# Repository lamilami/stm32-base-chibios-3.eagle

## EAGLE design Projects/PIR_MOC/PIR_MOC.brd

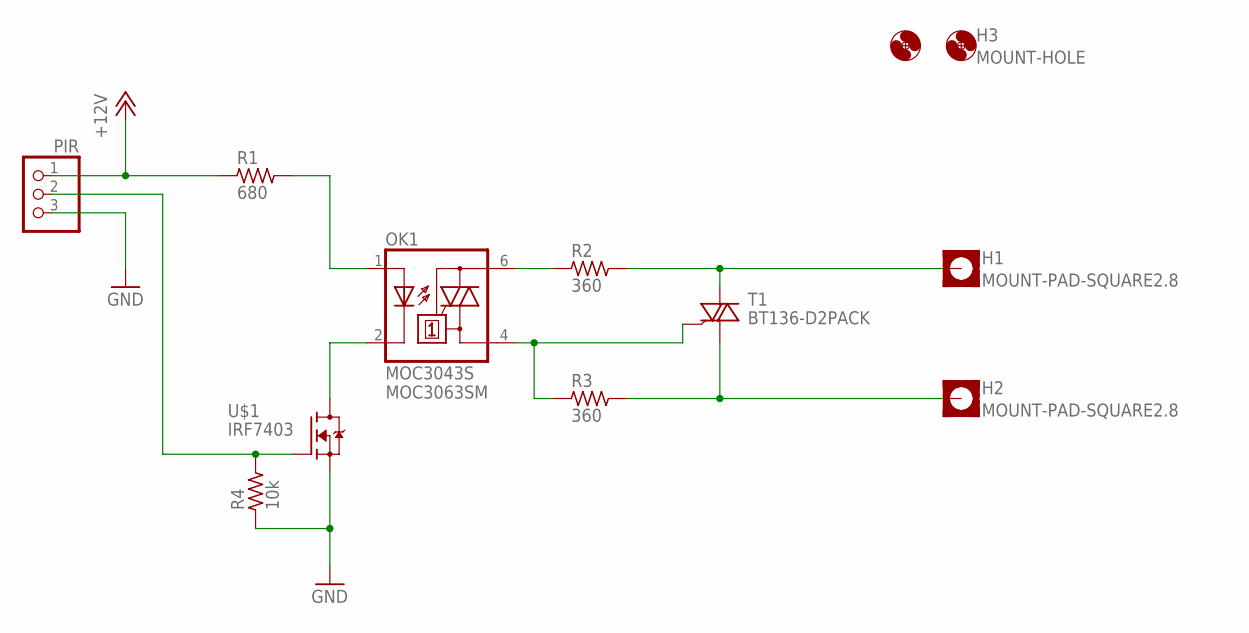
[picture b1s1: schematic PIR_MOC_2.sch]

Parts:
H1, H2: MOUNT-PAD-SQUARE2.8; 2,8-PAD-SQUARE
H3: MOUNT-HOLE; CASE_20-31_VHOLES
OK1: MOC3043S; DIL6-SMD; MPN MOC3063SM
PIR: PINHD-1X03_2.54-S; 1X03-S
R1: 680; R1206
R2, R3: 360; R1206
R4: 10k; R1206
T1: BT136-D2PACK; TO263
U$1: IRF7403; SO-8

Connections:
220_AC: H1.B2,8, R2.2, T1.3 (A2)
220_MOC_AC: OK1.6 (A2), R2.1
220_MOC_N: OK1.4 (A1), R3.1, T1.2 (G)
220_N: H2.B2,8, R3.2, T1.1 (A1)
+12V: PIR.1, R1.1
GND: PIR.3, R4.1, U$1.1 (S), U$1.2 (S), U$1.3 (S)
unnamed: OK1.2 (C), U$1.5 (D), U$1.6 (D), U$1.7 (D), U$1.8 (D)
unnamed: OK1.1 (A), R1.2
unnamed: PIR.2, R4.2, U$1.4 (G)

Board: 2 copper layers, 11 parts (0 on the bottom side), 9 nets, no tracks yet.

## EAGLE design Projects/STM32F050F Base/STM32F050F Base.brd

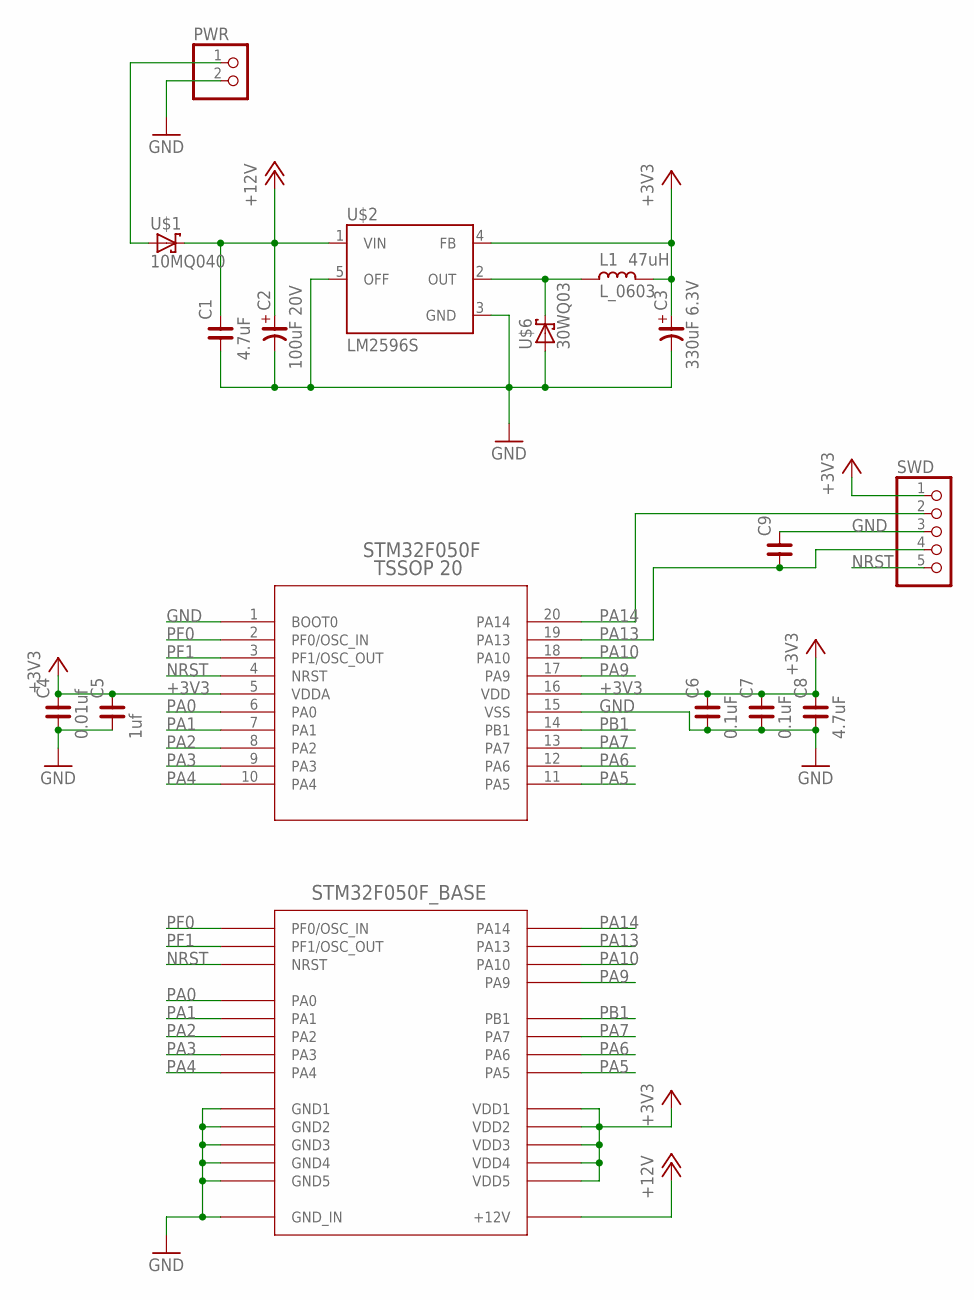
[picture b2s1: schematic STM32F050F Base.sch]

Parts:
C1, C8: 4.7uF; C1206
C2: 100uF 20V; C7343/T
C3: 330uF 6.3V; C7343/T
C4: 0.01uf; C0805
C5: 1uf; C0805
C6, C7: 0.1uF; C0805
C9: C_1206; C1206
L1: L_0603; L0603
PWR: PINHD-1X02_2.54-90°-S; 1X02/90-S
SWD: PINHD-1X05_2.54-90°-S; 1X05/90-S
U$1: 10MQ040; SMA
U$2: LM2596S; TO263-5
U$4: STM32F050F4P6; TSSOP20
U$5: STM32F050F_BASE_BASE; STM32_BASE
U$6: 30WQ03; TO252

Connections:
+3V3: C3.+, C4.2, C5.2, C6.2, C7.2, C8.2, L1.1, SWD.1, U$2.4 (FB), U$4.5 (VDDA), U$4.16 (VDD), U$5.VDD1, U$5.VDD2, U$5.VDD3, U$5.VDD4, U$5.VDD5
+12V: C1.2, C2.+, U$1.C, U$2.1 (VIN), U$5.+12V
GND: C1.1, C2.-, C3.-, C4.1, C5.1, C6.1, C7.1, C8.1, C9.2, PWR.2, SWD.3, U$2.3 (GND), U$2.5 (OFF), U$4.1 (BOOT0), U$4.15 (VSS), U$5.GND1, U$5.GND2, U$5.GND3, U$5.GND4, U$5.GND5, U$5.GND_IN, U$6.1 (A), U$6.2 (A)
unnamed: PWR.1, U$1.A
unnamed: L1.2, U$2.2 (OUT), U$6.3 (C)
NRST: SWD.5, U$4.4 (NRST), U$5.NRST
PA0: U$4.6 (PA0), U$5.PA0
PA1: U$4.7 (PA1), U$5.PA1
PA2: U$4.8 (PA2), U$5.PA2
PA3: U$4.9 (PA3), U$5.PA3
PA4: U$4.10 (PA4), U$5.PA4
PA5: U$4.11 (PA5), U$5.PA5
PA6: U$4.12 (PA6), U$5.PA6
PA7: U$4.13 (PA7), U$5.PA7
PA9: U$4.17 (PA9), U$5.PA9
PA10: U$4.18 (PA10), U$5.PA10
PA13: C9.1, SWD.4, U$4.19 (PA13), U$5.PA13
PA14: SWD.2, U$4.20 (PA14), U$5.PA14
PB1: U$4.14 (PB1), U$5.PB1
PF0: U$4.2 (PF0/OSC_IN), U$5.PF0 (PF0/OSC_IN)
PF1: U$4.3 (PF1/OSC_OUT), U$5.PF1 (PF1/OSC_OUT)

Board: 2 copper layers, 17 parts (0 on the bottom side), 21 nets, no tracks yet.

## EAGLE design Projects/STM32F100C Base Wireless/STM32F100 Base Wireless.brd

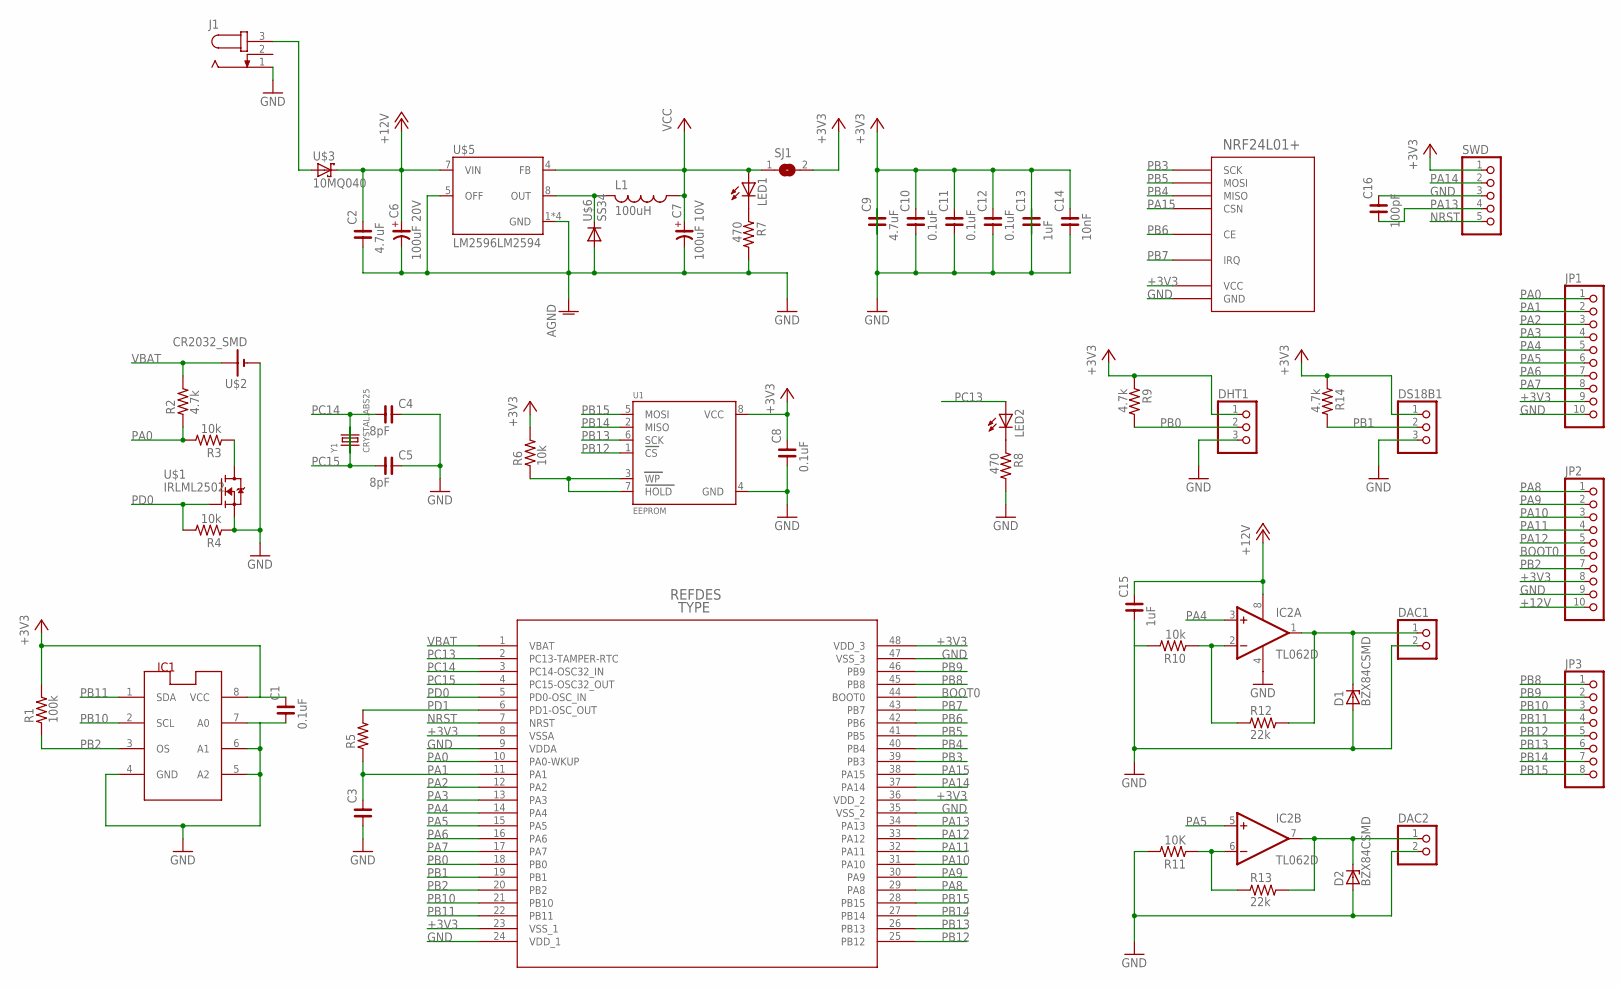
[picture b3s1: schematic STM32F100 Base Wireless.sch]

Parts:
C1, C8: 0.1uF; C1206
C2, C9: 4.7uF; C1206
C3: C_1206; C1206
C4, C5: 8pF; C0603
C6: 100uF 20V; C7343/T
C7: 100uF 10V; C6032-28/T
C10, C11, C12: 0.1uF; C0603
C13, C15: 1uF; C1206
C14: 10nF; C0603
C16: 100pF; C1206
D1, D2: BZX84CSMD; TO236
DAC1, DAC2: PINHD-1X02_2.54-S; 1X02-S
DHT1: PINHD-1X03_2.54-S; 1X03-S
DS18B1: PINHD-1X03_2.54-S; 1X03-S
IC1: LM75_ICN; SO8_LM75
IC2: TL062D; SO08
J1: JACK-PLUG0; SPC4077
JP1, JP2: PINHD-1X10_2.54-S; 1X10-S
JP3: PINHD-1X08_2.54-S; 1X08-S
L1: 100uH; POWER-CHOKE_WE-TPC
LED1, LED2: LEDCHIPLED_1206; CHIPLED_1206
R1: 100k; R1206
R2, R9, R14: 4.7k; R1206
R3, R4, R6, R10: 10k; R1206
R5: R_1206; R1206
R7, R8: 470; R1206
R11: 10K; R1206
R12, R13: 22k; R1206
SJ1: SJ
SWD: PINHD-1X05_2.54-90°-S; 1X05/90-S
U1: EEPROM; SOIC8_150MIL
U$1: IRLML2502; SOT23
U$2: CR2032_SMD; SMD_BH-2
U$3: 10MQ040; SMA
U$4: STM32F100C8T6B; LQFP-48
U$5: LM2596LM2594; SOIC8_150MIL
U$6: SS34; DO214AC
U$7: NRF24L01+
Y1: CRYSTAL.ABS25; ABS25

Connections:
+3V3: C1.2, C8.2, C9.1, C10.2, C11.2, C12.2, C13.1, C14.2, DHT1.1, DS18B1.1, IC1.8 (VCC), JP1.9, JP2.8, R1.2, R6.2, R9.1, R14.1, SJ1.2, SWD.1, U1.8 (VCC), U$4.8 (VSSA), U$4.23 (VSS_1), U$4.36 (VDD_2), U$4.48 (VDD_3), U$7.VCC
+12V: C2.2, C6.+, C15.2, IC2.8 (V+), JP2.10, U$3.C, U$5.7 (VIN)
BOOT0: JP2.6, U$4.44 (BOOT0)
GND: C1.1, C2.1, C3.1, C4.2, C5.2, C6.-, C7.-, C8.1, C9.2, C10.1, C11.1, C12.1, C13.2, C14.1, C15.1, C16.2, D1.A, D2.A, DAC1.2, DAC2.2, DHT1.3, DS18B1.3, IC1.4 (GND), IC1.5 (A2), IC1.6 (A1), IC1.7 (A0), IC2.4 (V-), J1.1, JP1.10, JP2.9, R4.1, R7.2, R8.2, R10.2, R11.2, SWD.3, U1.4 (GND), U$1.2 (S), U$2.P$NEG (-), U$4.9 (VDDA), U$4.24 (VDD_1), U$4.35 (VSS_2), U$4.47 (VSS_3), U$5.1 (GND), U$5.2 (GND), U$5.3 (GND), U$5.5 (OFF), U$5.6 (GND), U$6.A, U$7.GND
IN_12V: J1.3, U$3.A
LM_OUT: L1.2, U$5.8 (OUT), U$6.C
LM_VCC: C7.+, L1.1, LED1.A, SJ1.1, U$5.4 (FB)
unnamed: D1.C, DAC1.1, IC2.1 (OUT), R12.2
unnamed: LED1.C, R7.1
unnamed: IC2.2 (-IN), R10.1, R12.1
unnamed: IC2.6 (-IN), R11.1, R13.1
unnamed: D2.C, DAC2.1, IC2.7 (OUT), R13.2
unnamed: R3.1, U$1.3 (D)
unnamed: LED2.C, R8.1
unnamed: R6.1, U1.3 (WP), U1.7 (HOLD)
NRST: SWD.5, U$4.7 (NRST)
PA0: JP1.1, R2.1, R3.2, U$4.10 (PA0-WKUP)
PA1: C3.2, JP1.2, R5.1, U$4.11 (PA1)
PA2: JP1.3, U$4.12 (PA2)
PA3: JP1.4, U$4.13 (PA3)
PA4: IC2.3 (+IN), JP1.5, U$4.14 (PA4)
PA5: IC2.5 (+IN), JP1.6, U$4.15 (PA5)
PA6: JP1.7, U$4.16 (PA6)
PA7: JP1.8, U$4.17 (PA7)
PA8: JP2.1, U$4.29 (PA8)
PA9: JP2.2, U$4.30 (PA9)
PA10: JP2.3, U$4.31 (PA10)
PA11: JP2.4, U$4.32 (PA11)
PA12: JP2.5, U$4.33 (PA12)
PA13: C16.1, SWD.4, U$4.34 (PA13)
PA14: SWD.2, U$4.37 (PA14)
PA15: U$4.38 (PA15), U$7.CSN
PB0: DHT1.2, R9.2, U$4.18 (PB0)
PB1: DS18B1.2, R14.2, U$4.19 (PB1)
PB2: IC1.3 (OS), JP2.7, R1.1, U$4.20 (PB2)
PB3: U$4.39 (PB3), U$7.SCK
PB4: U$4.40 (PB4), U$7.MISO
PB5: U$4.41 (PB5), U$7.MOSI
PB6: U$4.42 (PB6), U$7.CE
PB7: U$4.43 (PB7), U$7.IRQ
PB8: JP3.1, U$4.45 (PB8)
PB9: JP3.2, U$4.46 (PB9)
PB10: IC1.2 (SCL), JP3.3, U$4.21 (PB10)
PB11: IC1.1 (SDA), JP3.4, U$4.22 (PB11)
PB12: JP3.5, U1.1 (CS), U$4.25 (PB12)
PB13: JP3.6, U1.6 (SCK), U$4.26 (PB13)
PB14: JP3.7, U1.2 (MISO), U$4.27 (PB14)
PB15: JP3.8, U1.5 (MOSI), U$4.28 (PB15)
PC13: LED2.A, U$4.2 (PC13-TAMPER-RTC)
PC14: C4.1, U$4.3 (PC14-OSC32_IN), Y1.1
PC15: C5.1, U$4.4 (PC15-OSC32_OUT), Y1.4 (2)
PD0: R4.2, U$1.1 (G), U$4.5 (PD0-OSC_IN)
PD1: R5.2, U$4.6 (PD1-OSC_OUT)
VBAT: R2.2, U$2.P$POS1 (+), U$4.1 (VBAT)

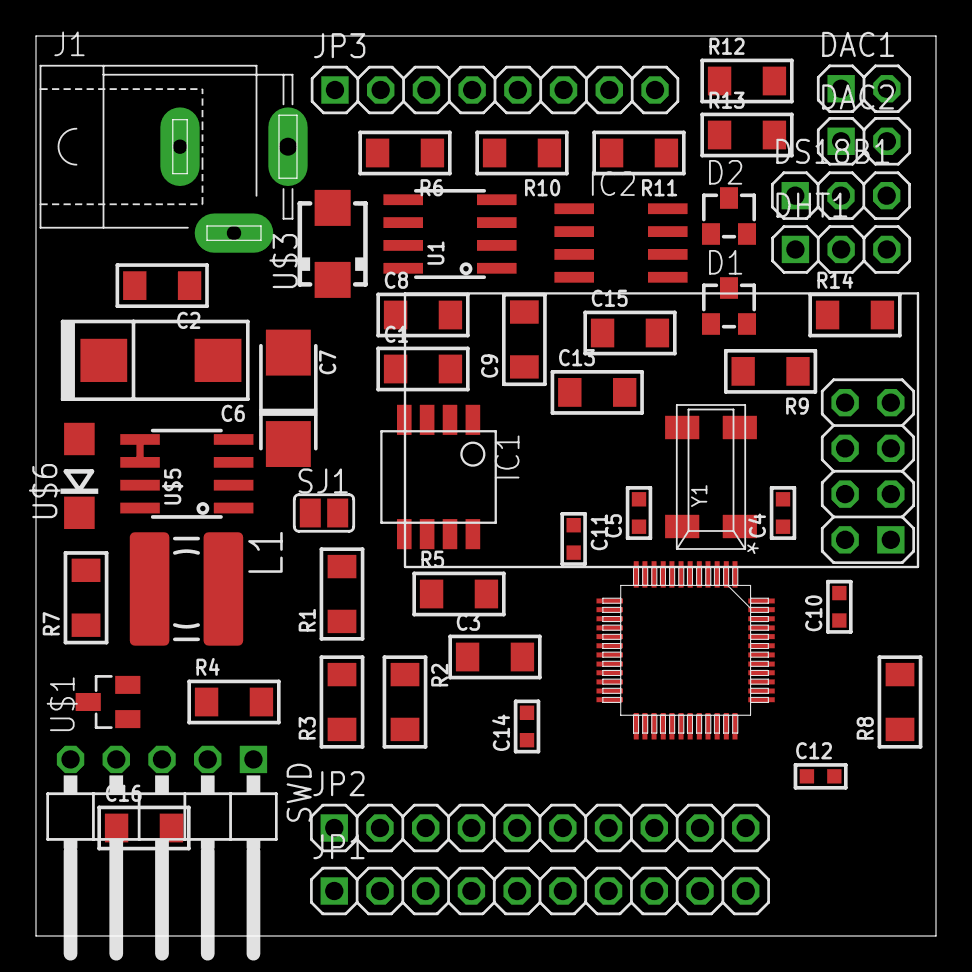
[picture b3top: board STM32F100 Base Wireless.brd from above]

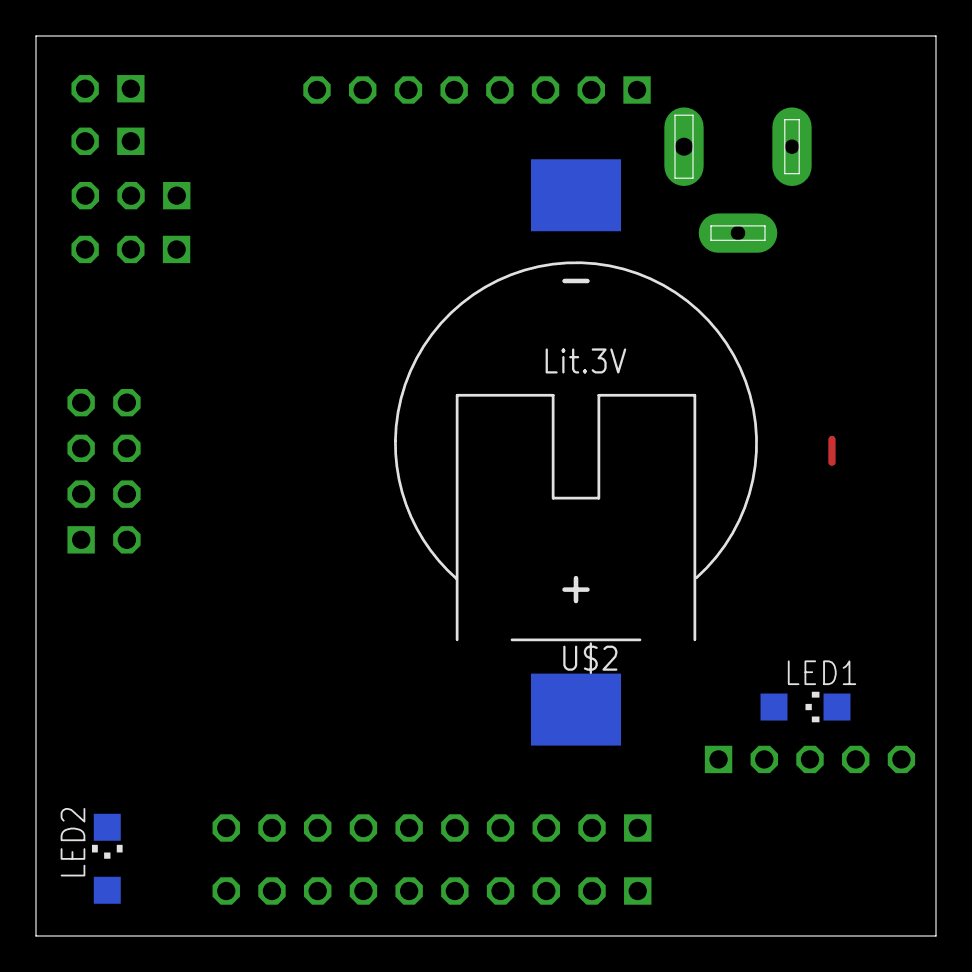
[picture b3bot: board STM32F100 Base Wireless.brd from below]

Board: 2 copper layers, 50.0 x 50.0 mm, 56 parts (3 on the bottom side), 54 nets.

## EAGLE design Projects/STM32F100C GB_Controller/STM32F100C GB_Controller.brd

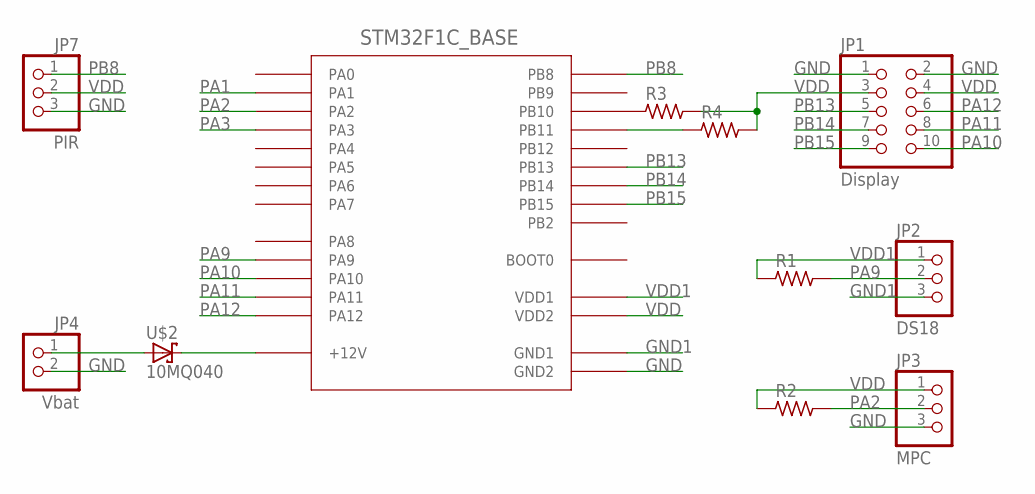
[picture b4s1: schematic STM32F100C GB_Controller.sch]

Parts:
JP1: Display; 2X05
JP2: DS18; 1X03-S
JP3: MPC; 1X03-S
JP4: Vbat; 1X02-S
JP7: PIR; 1X03-S
R1, R2, R3, R4: R_1206; R1206
U$1: STM32F1C_BASE; STM32F1_BASE
U$2: 10MQ040; SMA

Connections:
GND: JP1.1, JP1.2, JP3.3, JP4.2, JP7.3, U$1.GND1 (GND2)
GND1: JP2.3, U$1.GND (GND1)
unnamed: JP4.1, U$2.A
unnamed: R4.1, U$1.PB11
unnamed: R3.1, U$1.PB10
unnamed: U$1.+12 (+12V), U$2.C
PA1: U$1.PA1
PA2: JP3.2, R2.2, U$1.PA2
PA3: U$1.PA3
PA9: JP2.2, R1.2, U$1.PA9
PA10: JP1.10, U$1.PA10
PA11: JP1.8, U$1.PA11
PA12: JP1.6, U$1.PA12
PB8: JP7.1, U$1.PB8
PB13: JP1.5, U$1.PB13
PB14: JP1.7, U$1.PB14
PB15: JP1.9, U$1.PB15
VDD: JP1.3, JP1.4, JP3.1, JP7.2, R2.1, R3.2, R4.2, U$1.3.3_1 (VDD2)
VDD1: JP2.1, R1.1, U$1.3.3 (VDD1)

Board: 2 copper layers, 11 parts (2 on the bottom side), 17 nets, no tracks yet.

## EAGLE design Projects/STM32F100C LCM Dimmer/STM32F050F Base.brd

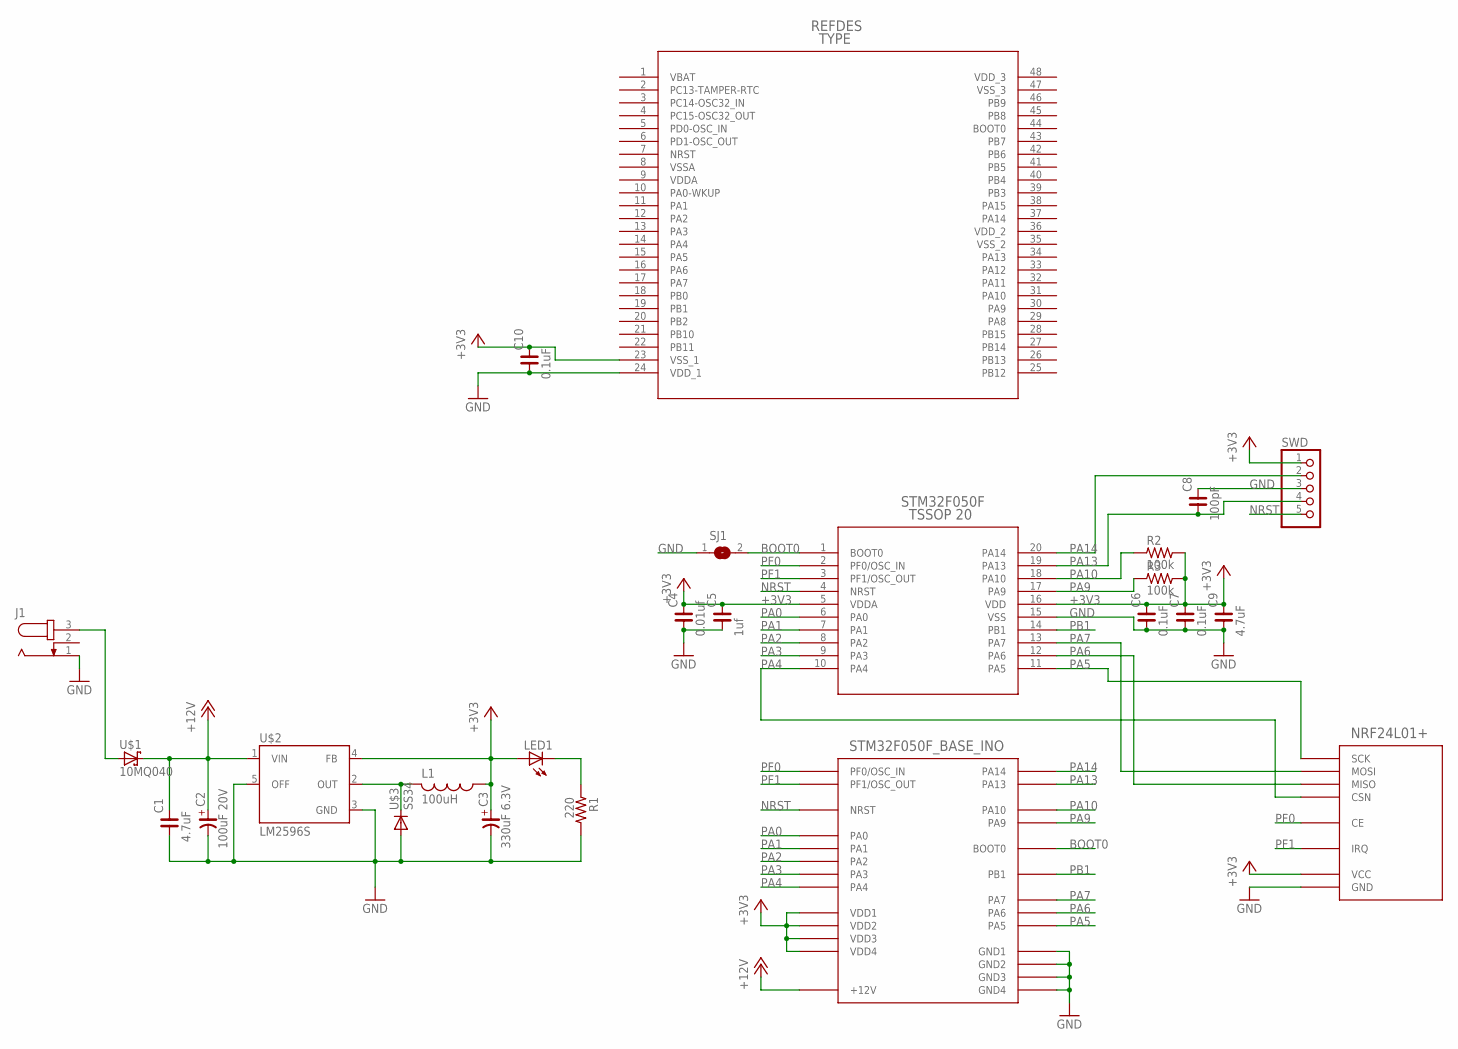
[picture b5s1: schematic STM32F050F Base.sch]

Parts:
C1, C9: 4.7uF; C1206
C2: 100uF 20V; C7343/T
C3: 330uF 6.3V; C7343/T
C4: 0.01uf; C1206
C5: 1uf; C1206
C6, C7, C10: 0.1uF; C1206
C8: 100pF; C1206
J1: JACK-PLUG0; SPC4077
L1: 100uH; POWER-CHOKE_WE-TPC
LED1: LEDCHIPLED_1206; CHIPLED_1206
R1: 220; R1206
R2, R3: 100k; R1206
SJ1: SJ
SWD: PINHD-1X05_2.54-90°-S; 1X05/90-S
U$1: 10MQ040; SMA
U$2: LM2596S; TO263-5
U$3: SS34; SMC
U$4: STM32F050F4P6; TSSOP20
U$5: STM32F050F_BASE_INO; STM32_BASE_INO
U$6: NRF24L01+
U$7: STM32F100C8T6B; LQFP-48

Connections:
+3V3: C3.+, C4.2, C5.2, C6.2, C7.2, C9.2, C10.2, L1.1, LED1.A, R2.2, R3.2, SWD.1, U$2.4 (FB), U$4.5 (VDDA), U$4.16 (VDD), U$5.VDD1, U$5.VDD2, U$5.VDD3, U$5.VDD4, U$6.VCC, U$7.23 (VSS_1)
+12V: C1.2, C2.+, U$1.C, U$2.1 (VIN), U$5.+12V
BOOT0: SJ1.2, U$4.1 (BOOT0), U$5.BOOT0
GND: C1.1, C2.-, C3.-, C4.1, C5.1, C6.1, C7.1, C8.2, C9.1, C10.1, J1.1, R1.2, SJ1.1, SWD.3, U$2.3 (GND), U$2.5 (OFF), U$3.A, U$4.15 (VSS), U$5.GND1, U$5.GND2, U$5.GND3, U$5.GND4, U$6.GND, U$7.24 (VDD_1)
unnamed: LED1.C, R1.1
unnamed: J1.3, U$1.A
unnamed: L1.2, U$2.2 (OUT), U$3.C
NRST: SWD.5, U$4.4 (NRST), U$5.NRST
PA0: U$4.6 (PA0), U$5.PA0
PA1: U$4.7 (PA1), U$5.PA1
PA2: U$4.8 (PA2), U$5.PA2
PA3: U$4.9 (PA3), U$5.PA3
PA4: U$4.10 (PA4), U$5.PA4, U$6.CSN
PA5: U$4.11 (PA5), U$5.PA5, U$6.SCK
PA6: U$4.12 (PA6), U$5.PA6, U$6.MISO
PA7: U$4.13 (PA7), U$5.PA7, U$6.MOSI
PA9: R3.1, U$4.17 (PA9), U$5.PA9
PA10: R2.1, U$4.18 (PA10), U$5.PA10
PA13: C8.1, SWD.4, U$4.19 (PA13), U$5.PA13
PA14: SWD.2, U$4.20 (PA14), U$5.PA14
PB1: U$4.14 (PB1), U$5.PB1
PF0: U$4.2 (PF0/OSC_IN), U$5.PF0 (PF0/OSC_IN), U$6.CE
PF1: U$4.3 (PF1/OSC_OUT), U$5.PF1 (PF1/OSC_OUT), U$6.IRQ

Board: 2 copper layers, 25 parts (3 on the bottom side), 23 nets, no tracks yet.

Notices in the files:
parts and their libraries:
rc-master-smd: Copyright (C) 2007, Bob Starr
